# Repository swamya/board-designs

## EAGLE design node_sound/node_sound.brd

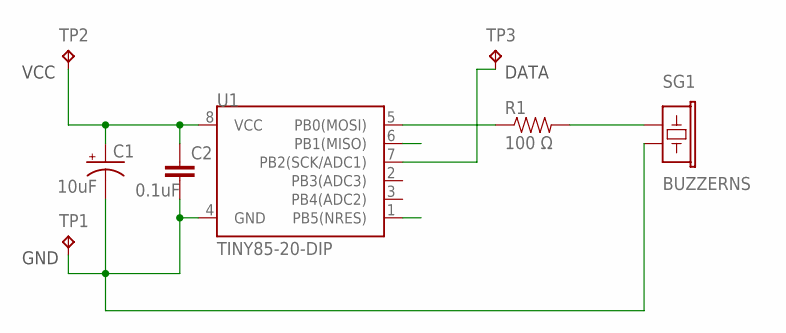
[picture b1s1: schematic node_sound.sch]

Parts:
C1: 10uF; EIA3216
C2: 0.1uF; 1206
R1: 100 Ω; 1206
SG1: BUZZERNS; BUZZER-12MM-NS
TP1, TP2, TP3: PADSTP13R; CIRCLE-PAD-1/4
U1: TINY85-20-DIP; DIP08

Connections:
GND: C1.C (-), C2.2, SG1.- (2), TP1.TP, U1.4 (GND)
MISO-6: U1.6 (PB1(MISO))
MOSI-5: R1.1, U1.5 (PB0(MOSI))
unnamed: R1.2, SG1.+ (1)
RST: U1.1 (PB5(NRES))
SCK-7: TP3.TP, U1.7 (PB2(SCK/ADC1))
VCC: C1.A (+), C2.1, TP2.TP, U1.8 (VCC)

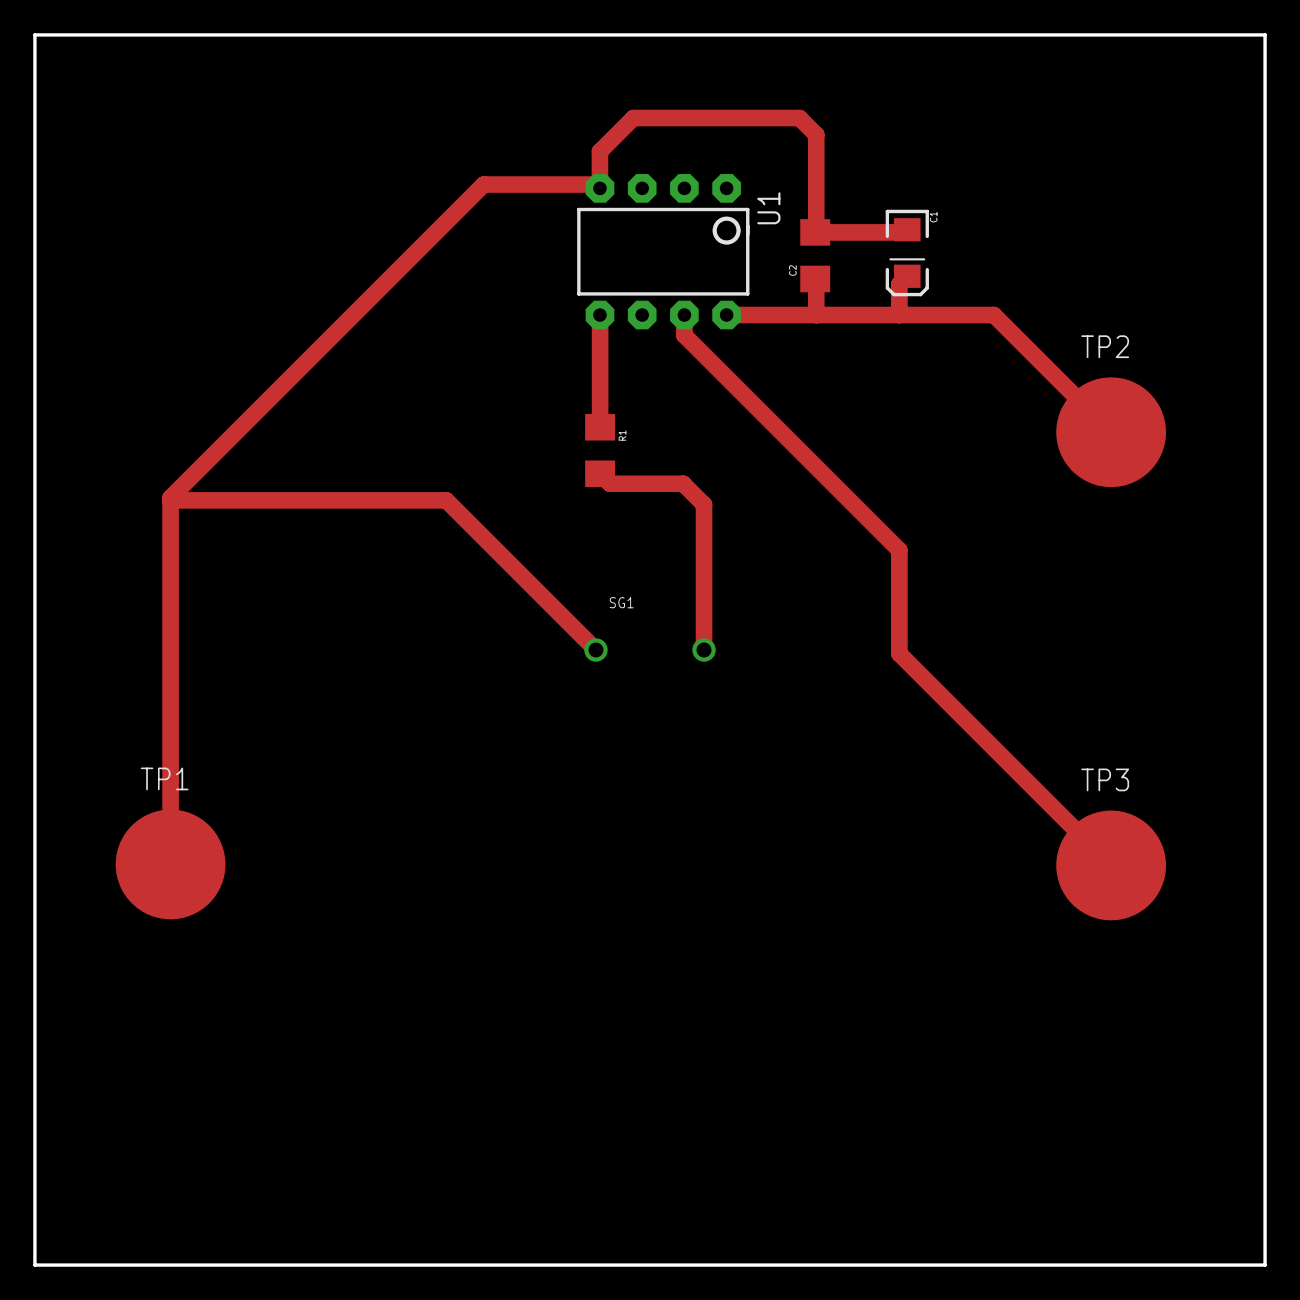
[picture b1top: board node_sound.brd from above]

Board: 2 copper layers, 74.0 x 74.0 mm, 8 parts (0 on the bottom side), 5 nets.

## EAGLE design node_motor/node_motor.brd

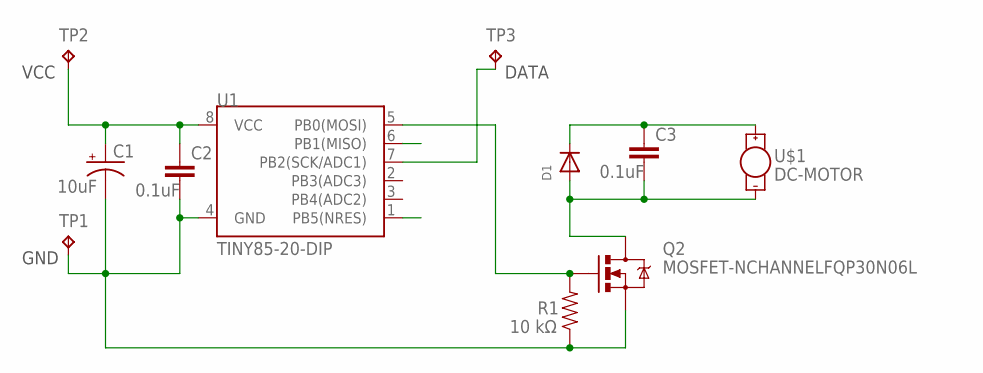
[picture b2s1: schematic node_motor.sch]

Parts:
C1: 10uF; EIA3216
C2, C3: 0.1uF; 1206
D1: DIODESMA; SMADIODE
Q2: MOSFET-NCHANNELFQP30N06L; TO220V
R1: 10 kΩ; 1206
TP1, TP2, TP3: PADSTP13R; CIRCLE-PAD-1/4
U1: TINY85-20-DIP; DIP08
U$1: DC-MOTOR; DC-MOTOR-20MM

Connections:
GND: C1.C (-), C2.2, Q2.3 (S), R1.1, TP1.TP, U1.4 (GND)
MISO-6: U1.6 (PB1(MISO))
unnamed: Q2.1 (G), R1.2, U1.5 (PB0(MOSI))
unnamed: C3.2, D1.A, Q2.2 (D), U$1.-
unnamed: C3.1, D1.C, U$1.+
RST: U1.1 (PB5(NRES))
SCK-7: TP3.TP, U1.7 (PB2(SCK/ADC1))
VCC: C1.A (+), C2.1, TP2.TP, U1.8 (VCC)

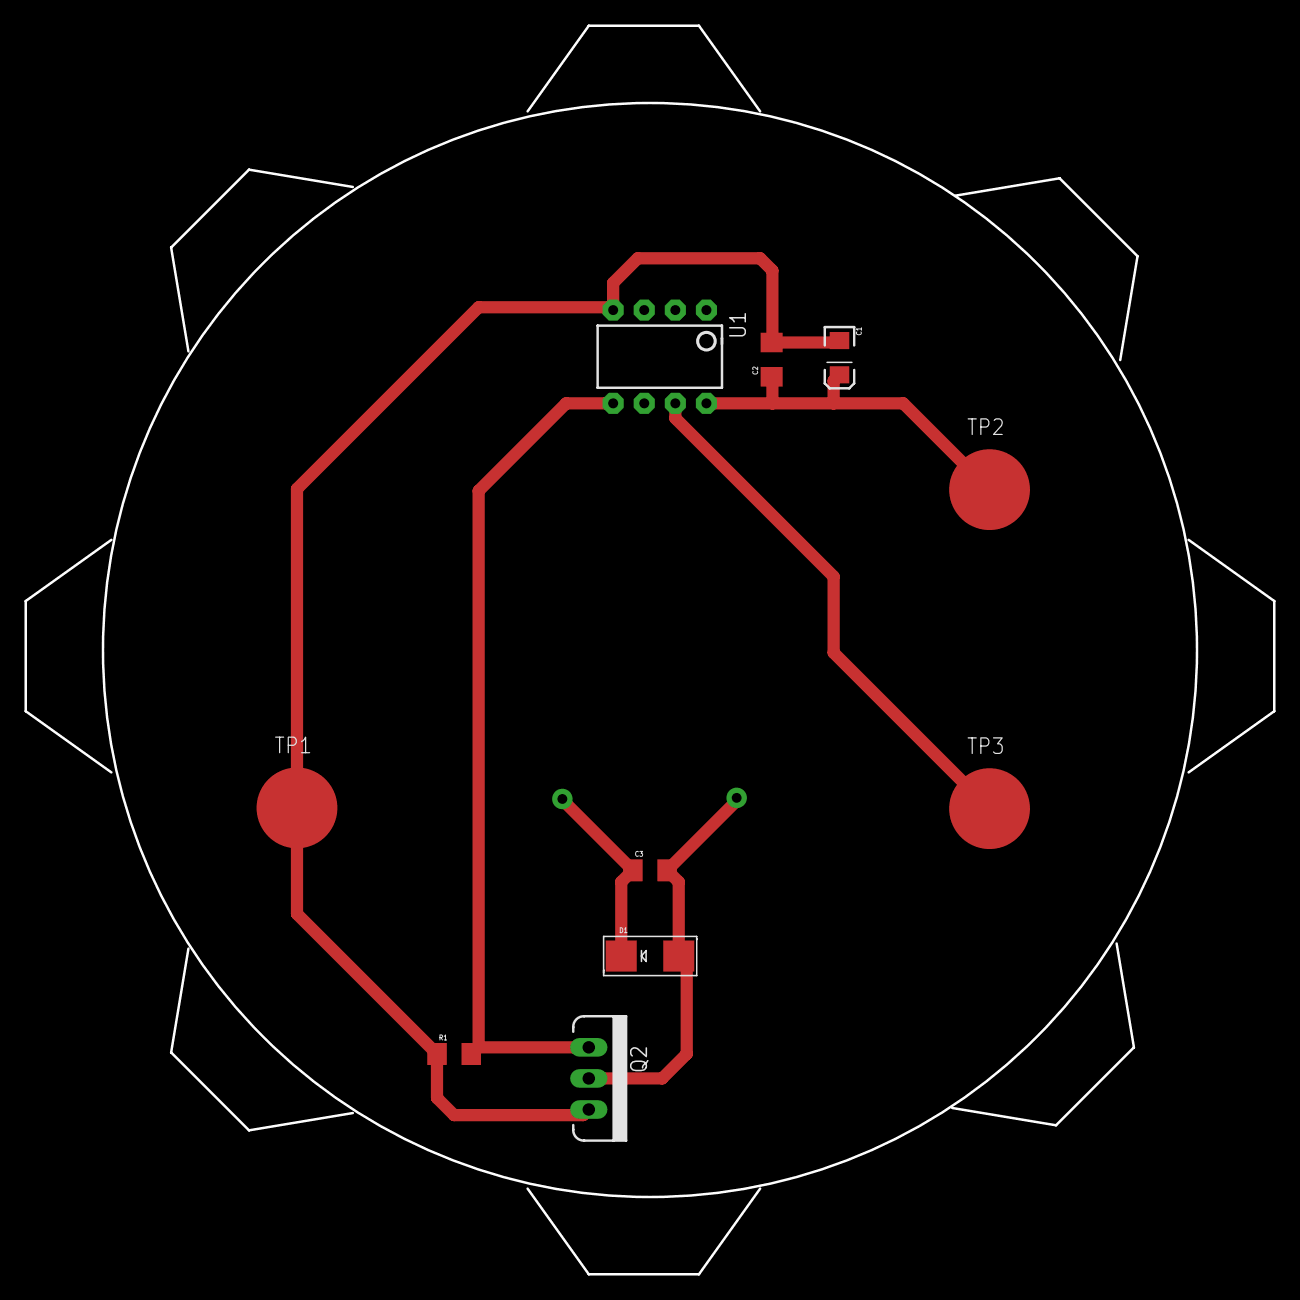
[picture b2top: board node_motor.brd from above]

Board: 2 copper layers, 89.4 x 89.4 mm, 11 parts (1 on the bottom side), 6 nets.

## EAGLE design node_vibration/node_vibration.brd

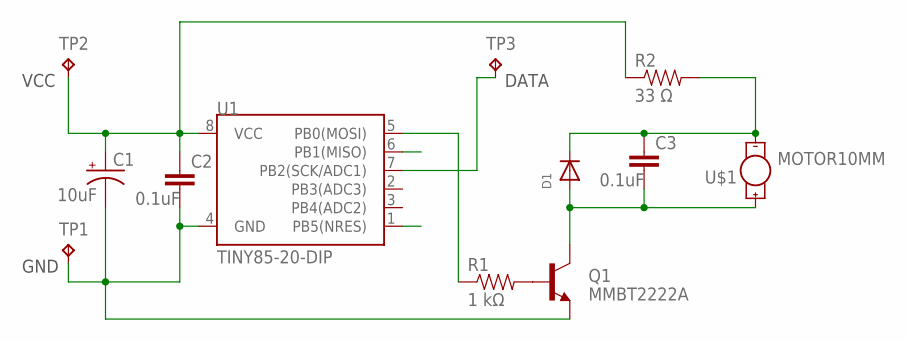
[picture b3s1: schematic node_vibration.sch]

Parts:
C1: 10uF; EIA3216
C2, C3: 0.1uF; 1206
D1: DIODESMA; SMADIODE
Q1: MMBT2222A; SOT23-3
R1: 1 kΩ; 1206
R2: 33 Ω; 1206
TP1, TP2, TP3: PADSTP13R; CIRCLE-PAD-1/4
U1: TINY85-20-DIP; DIP08
U$1: MOTOR10MM; VIBE-MOTOR-10MM

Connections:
GND: C1.C (-), C2.2, Q1.2 (E), TP1.TP, U1.4 (GND)
MISO-6: U1.6 (PB1(MISO))
MOSI-5: R1.1, U1.5 (PB0(MOSI))
unnamed: Q1.1 (B), R1.2
unnamed: C3.1, D1.C, R2.2, U$1.-
unnamed: C3.2, D1.A, Q1.3 (C), U$1.+
RST: U1.1 (PB5(NRES))
SCK-7: TP3.TP, U1.7 (PB2(SCK/ADC1))
VCC: C1.A (+), C2.1, R2.1, TP2.TP, U1.8 (VCC)

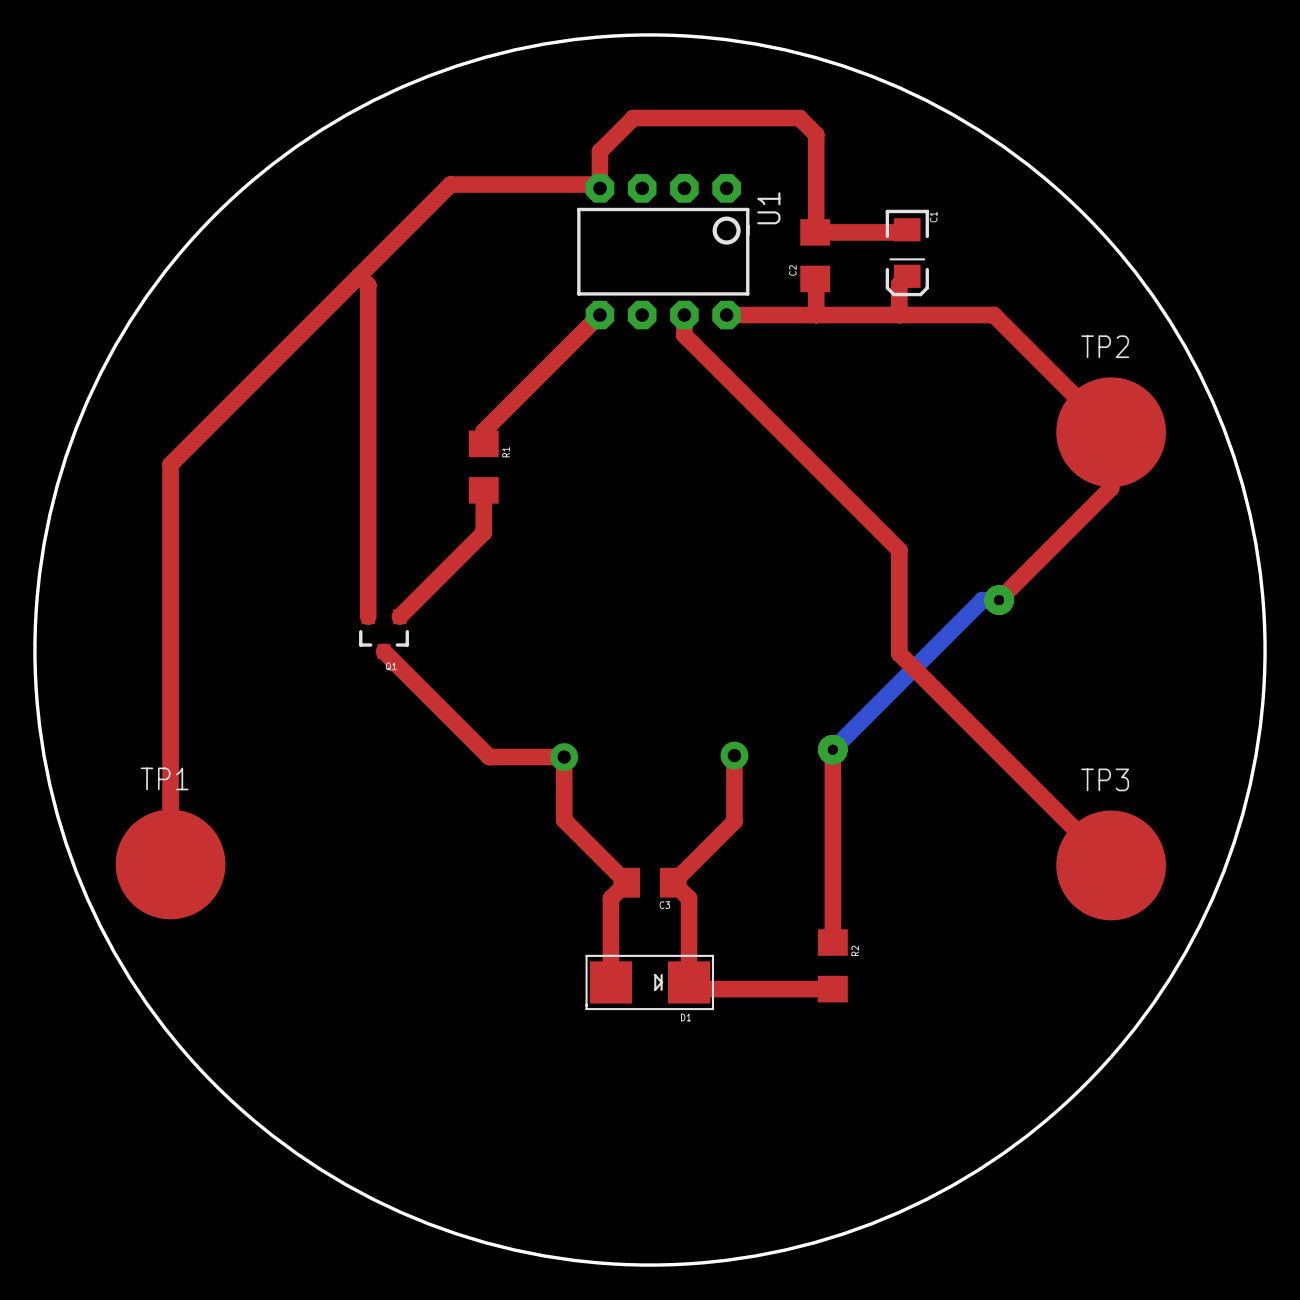
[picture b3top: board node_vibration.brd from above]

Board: 2 copper layers, 74.0 x 74.0 mm, 12 parts (1 on the bottom side), 7 nets.

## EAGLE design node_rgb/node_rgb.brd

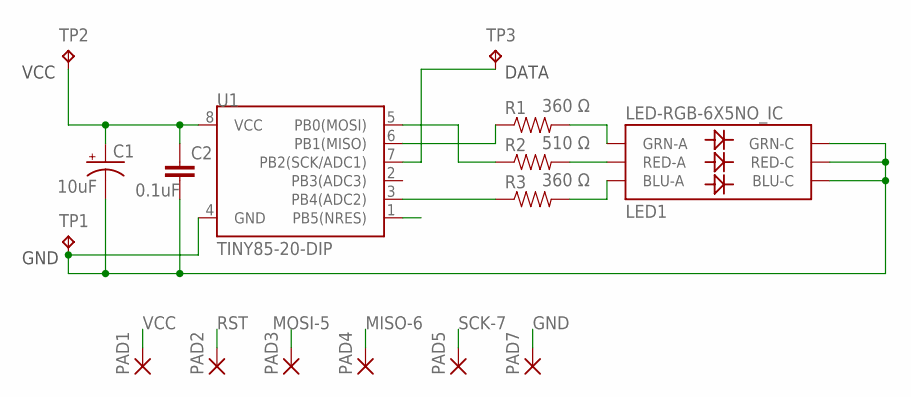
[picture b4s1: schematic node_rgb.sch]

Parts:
C1: 10uF; EIA3216
C2: 0.1uF; 1206
LED1: LED-RGB-6X5NO_IC; LED-RGB-6X5
PAD1, PAD2, PAD3, PAD4, PAD5, PAD7: SMD5; SMD2,54-5,08
R1, R3: 360 Ω; 1206
R2: 510 Ω; 1206
TP1, TP2, TP3: PADSTP13R; CIRCLE-PAD-1/4
U1: TINY85-20-DIP; DIP08

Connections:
ADC2: R3.1, U1.3 (PB4(ADC2))
GND: C1.C (-), C2.2, LED1.1 (BLU-C), LED1.2 (RED-C), LED1.3 (GRN-C), PAD7.1, TP1.TP, U1.4 (GND)
MISO-6: PAD4.1, R1.1, U1.6 (PB1(MISO))
MOSI-5: PAD3.1, R2.1, U1.5 (PB0(MOSI))
unnamed: LED1.4 (GRN-A), R1.2
unnamed: LED1.5 (RED-A), R2.2
unnamed: LED1.6 (BLU-A), R3.2
RST: PAD2.1, U1.1 (PB5(NRES))
SCK-7: PAD5.1, TP3.TP, U1.7 (PB2(SCK/ADC1))
VCC: C1.A (+), C2.1, PAD1.1, TP2.TP, U1.8 (VCC)

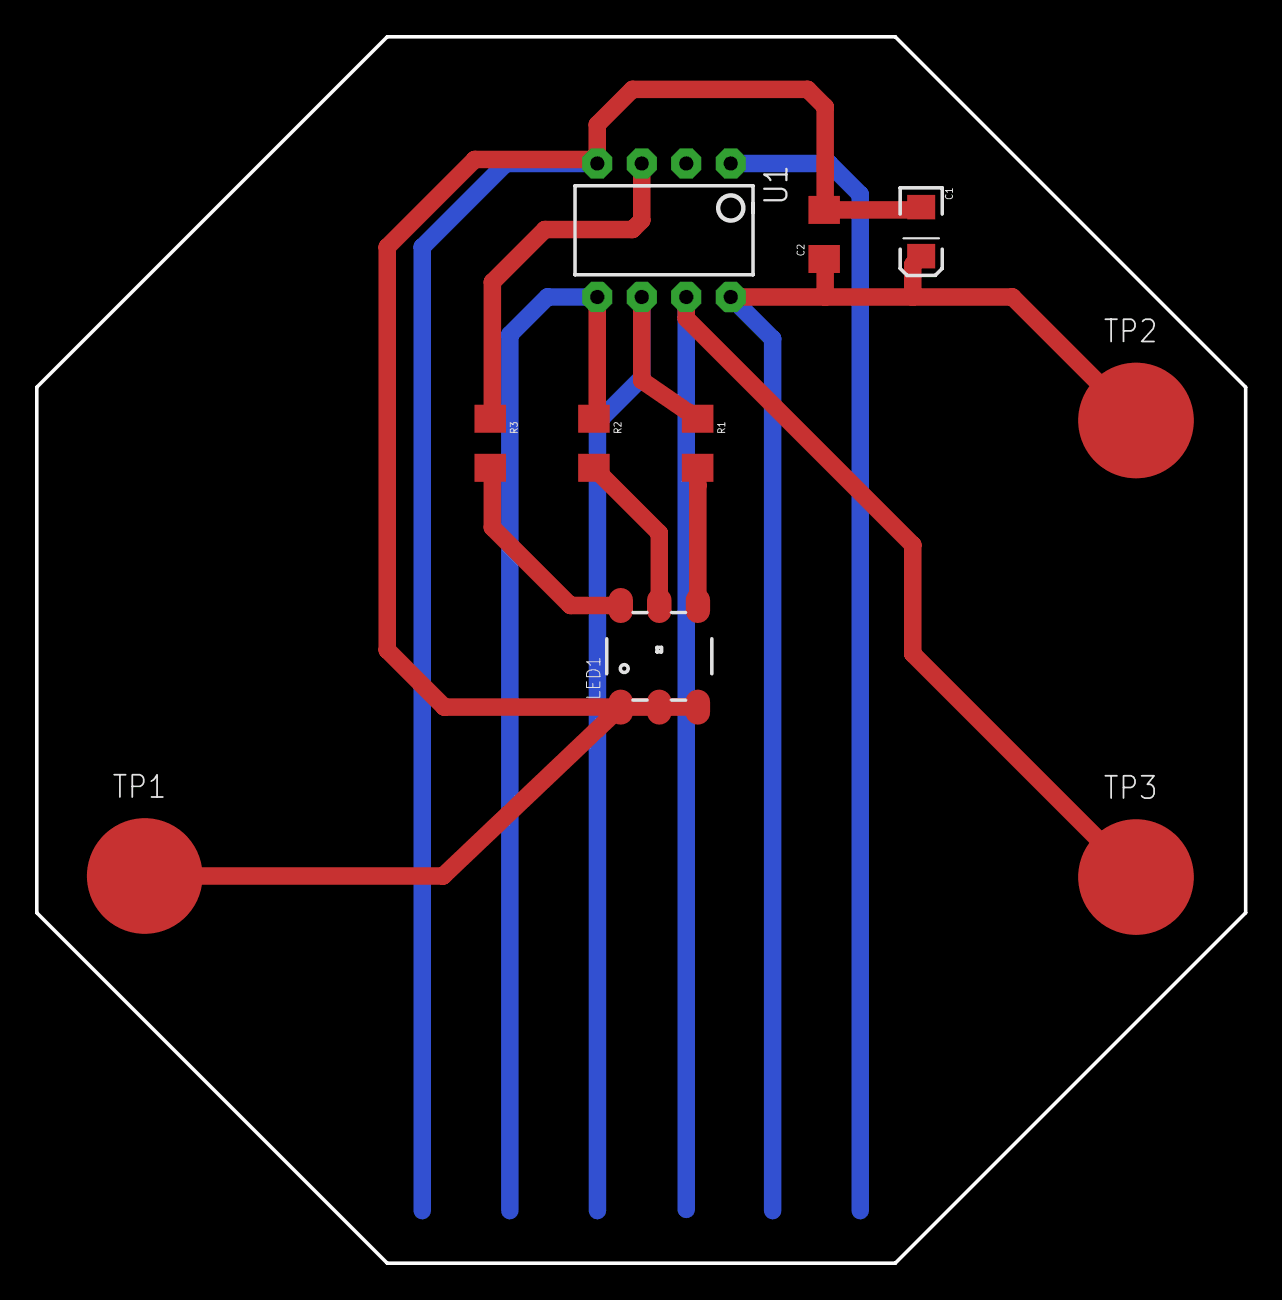
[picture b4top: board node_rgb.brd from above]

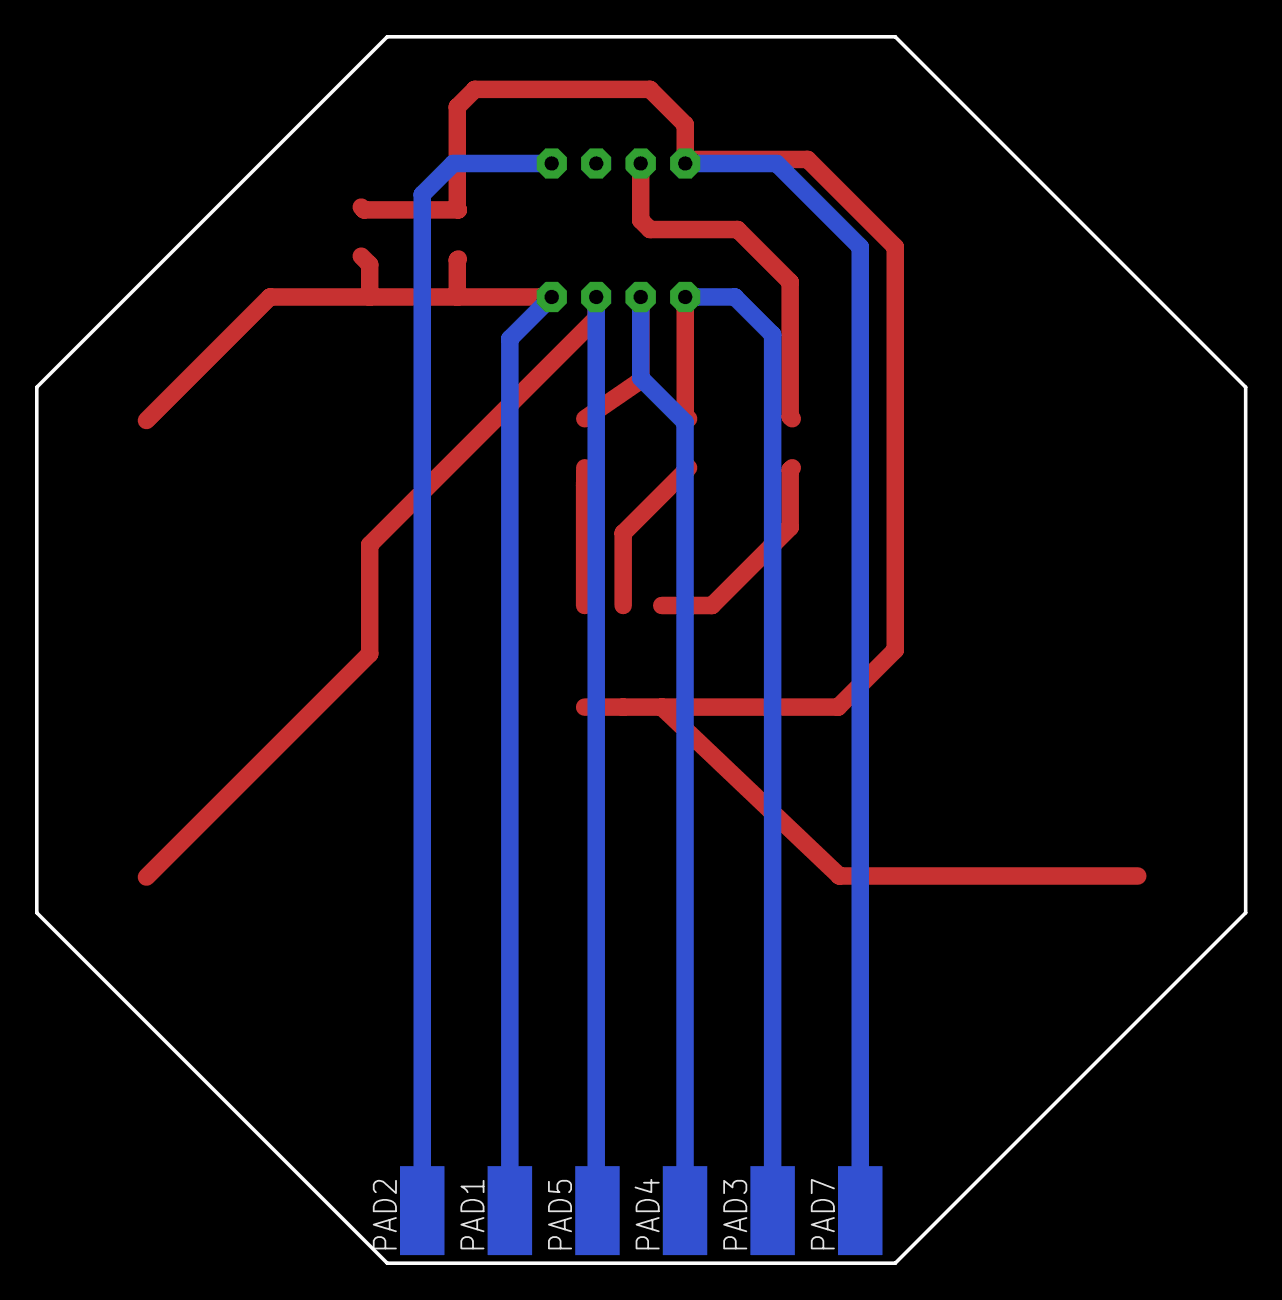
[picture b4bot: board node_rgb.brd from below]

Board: 2 copper layers, 69.0 x 70.0 mm, 16 parts (6 on the bottom side), 10 nets.

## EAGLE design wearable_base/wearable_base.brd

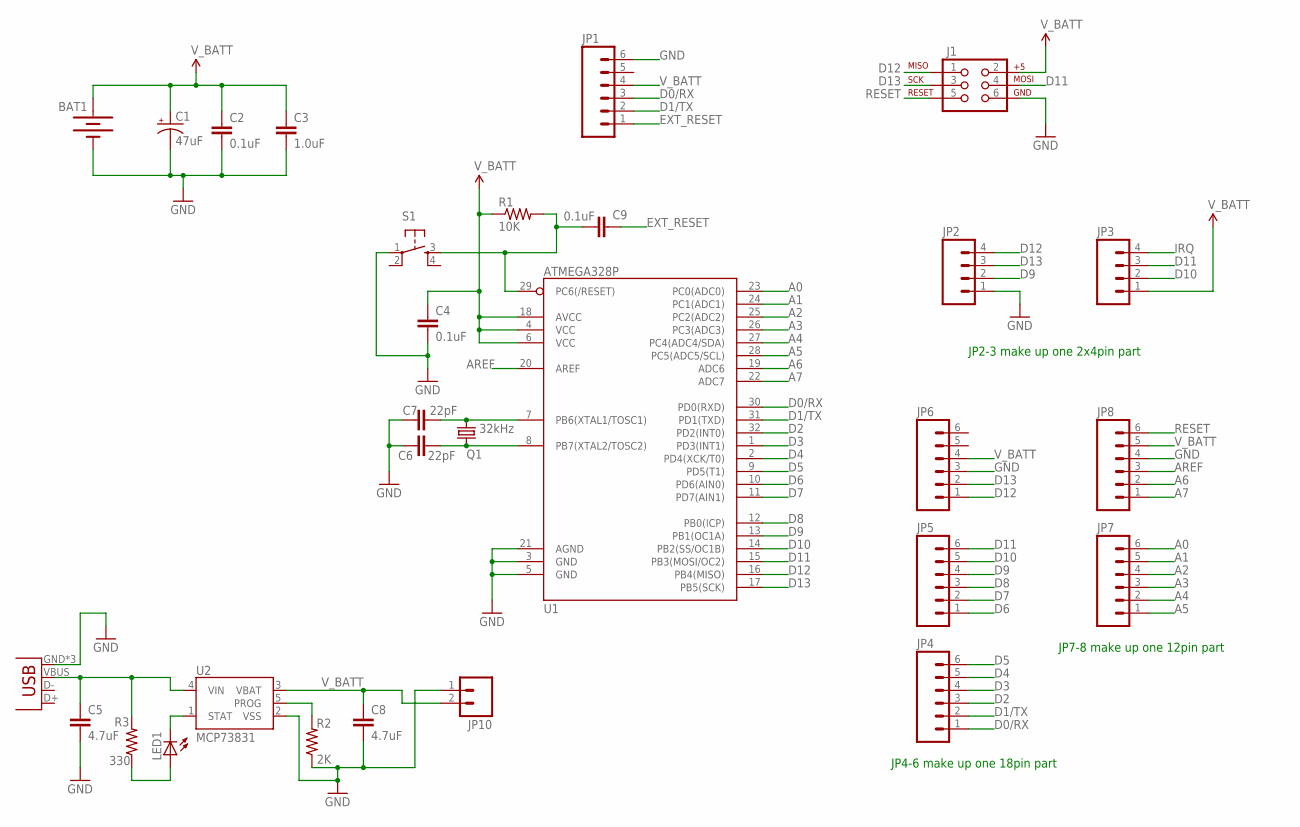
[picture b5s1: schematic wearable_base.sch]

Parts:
BAT1: 20mm coincell; BATTCON_20MM_4LEGS
C1: 47uF; EIA3216
C2, C4, C9: 0.1uF; 0603-CAP
C3: 1.0uF; 0603-CAP
C5, C8: 4.7uF; 0603-CAP
C6, C7: 22pF; 0603-CAP
J1: AVR_SPI_PRG_6PTH; 2X3
JP1, JP4, JP5, JP6, JP7, JP8: M06SIP; 1X06
JP2, JP3: M04PTH; 1X04
JP9: USB-MICROB
JP10: M02JST-PTH-2; JST-2-PTH
LED1: LED_ESML0603; LED_SML0603
Q1: 32kHz; TC26H
R1: 10K; 0603-RES
R2: 2K; 0603-RES
R3: 330; 0603-RES
S1: TAC_SWITCHSMD; TACTILE_SWITCH_SMD
U1: ATMEGA328P; TQFP32-08
U2: MCP73831; SOT23-5

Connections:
A0: JP7.6, U1.23 (PC0(ADC0))
A1: JP7.5, U1.24 (PC1(ADC1))
A2: JP7.4, U1.25 (PC2(ADC2))
A3: JP7.3, U1.26 (PC3(ADC3))
A4: JP7.2, U1.27 (PC4(ADC4/SDA))
A5: JP7.1, U1.28 (PC5(ADC5/SCL))
A6: JP8.2, U1.19 (ADC6)
A7: JP8.1, U1.22 (ADC7)
AREF: JP8.3, U1.20 (AREF)
D0/RX: JP1.3, JP4.1, U1.30 (PD0(RXD))
D1/TX: JP1.2, JP4.2, U1.31 (PD1(TXD))
D2: JP4.3, U1.32 (PD2(INT0))
D3: JP4.4, U1.1 (PD3(INT1))
D4: JP4.5, U1.2 (PD4(XCK/T0))
D5: JP4.6, U1.9 (PD5(T1))
D6: JP5.1, U1.10 (PD6(AIN0))
D7: JP5.2, U1.11 (PD7(AIN1))
D8: JP5.3, U1.12 (PB0(ICP))
D9: JP2.2, JP5.4, U1.13 (PB1(OC1A))
D10: JP3.2, JP5.5, U1.14 (PB2(SS/OC1B))
D11: J1.4, JP3.3, JP5.6, U1.15 (PB3(MOSI/OC2))
D12: J1.1, JP2.4, JP6.1, U1.16 (PB4(MISO))
D13: J1.3, JP2.3, JP6.2, U1.17 (PB5(SCK))
EXT_RESET: C9.1, JP1.1
GND: BAT1.2 (-), C1.C (-), C2.2, C3.2, C4.2, C5.2, C6.1, C7.2, C8.2, J1.6, JP1.6, JP2.1, JP6.3, JP8.4, JP9.GND, JP9.MT1 (GND), JP9.MT2 (GND), JP10.1, R2.1, S1.1, U1.3 (GND), U1.5 (GND), U1.21 (AGND), U2.2 (VSS)
IRQ: JP3.4
unnamed: C7.1, Q1.2, U1.7 (PB6(XTAL1/TOSC1))
unnamed: C6.2, Q1.1, U1.8 (PB7(XTAL2/TOSC2))
unnamed: LED1.C, U2.1 (STAT)
unnamed: LED1.A, R3.1
unnamed: C5.1, JP9.VBUS, R3.2, U2.4 (VIN)
unnamed: R2.2, U2.5 (PROG)
RESET: C9.2, J1.5, JP8.6, R1.2, S1.3, U1.29 (PC6(/RESET))
V_BATT: BAT1.1 (+), C1.A (+), C2.1, C3.1, C4.1, C8.1, J1.2, JP1.4, JP3.1, JP6.4, JP8.5, JP10.2, R1.1, U1.4 (VCC), U1.6 (VCC), U1.18 (AVCC), U2.3 (VBAT)

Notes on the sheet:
JP4-6 make up one 18pin part
JP7-8 make up one 12pin part
JP2-3 make up one 2x4pin part

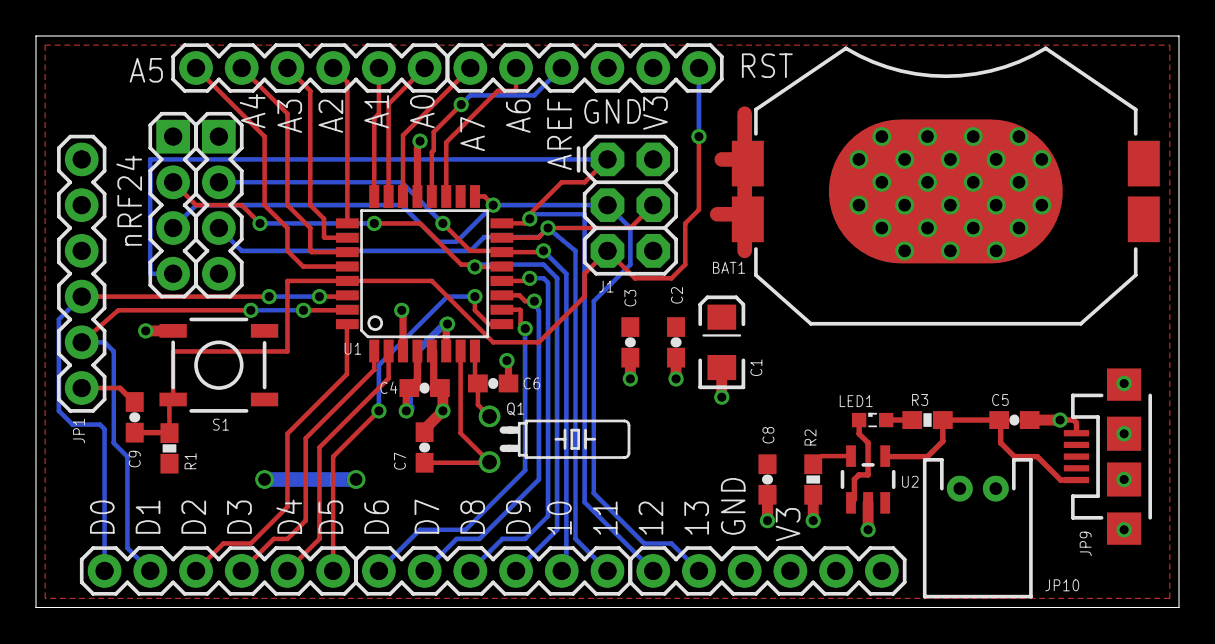
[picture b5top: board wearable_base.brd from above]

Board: 2 copper layers, 63.5 x 31.8 mm, 29 parts (0 on the bottom side), 33 nets.

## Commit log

2015-01-06 schematics and board diagrams for nodes
2015-01-20 added vibration symbols
2015-01-20 paper circuit for piezo speaker
2015-01-20 Placement updates
2015-01-20 Box dimension added
2015-01-21 eps and image files of circuit for laser cutter and paper cutter

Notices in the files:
parts and their libraries:
SparkFun-DigitalIC: Licensing: Creative Commons ShareAlike 4.0 International - https://creativecommons.org/licenses/by-sa/4.0
SparkFun-DigitalIC: Licensing: CC v3.0 Share-Alike You are welcome to use this library for commercial purposes.
